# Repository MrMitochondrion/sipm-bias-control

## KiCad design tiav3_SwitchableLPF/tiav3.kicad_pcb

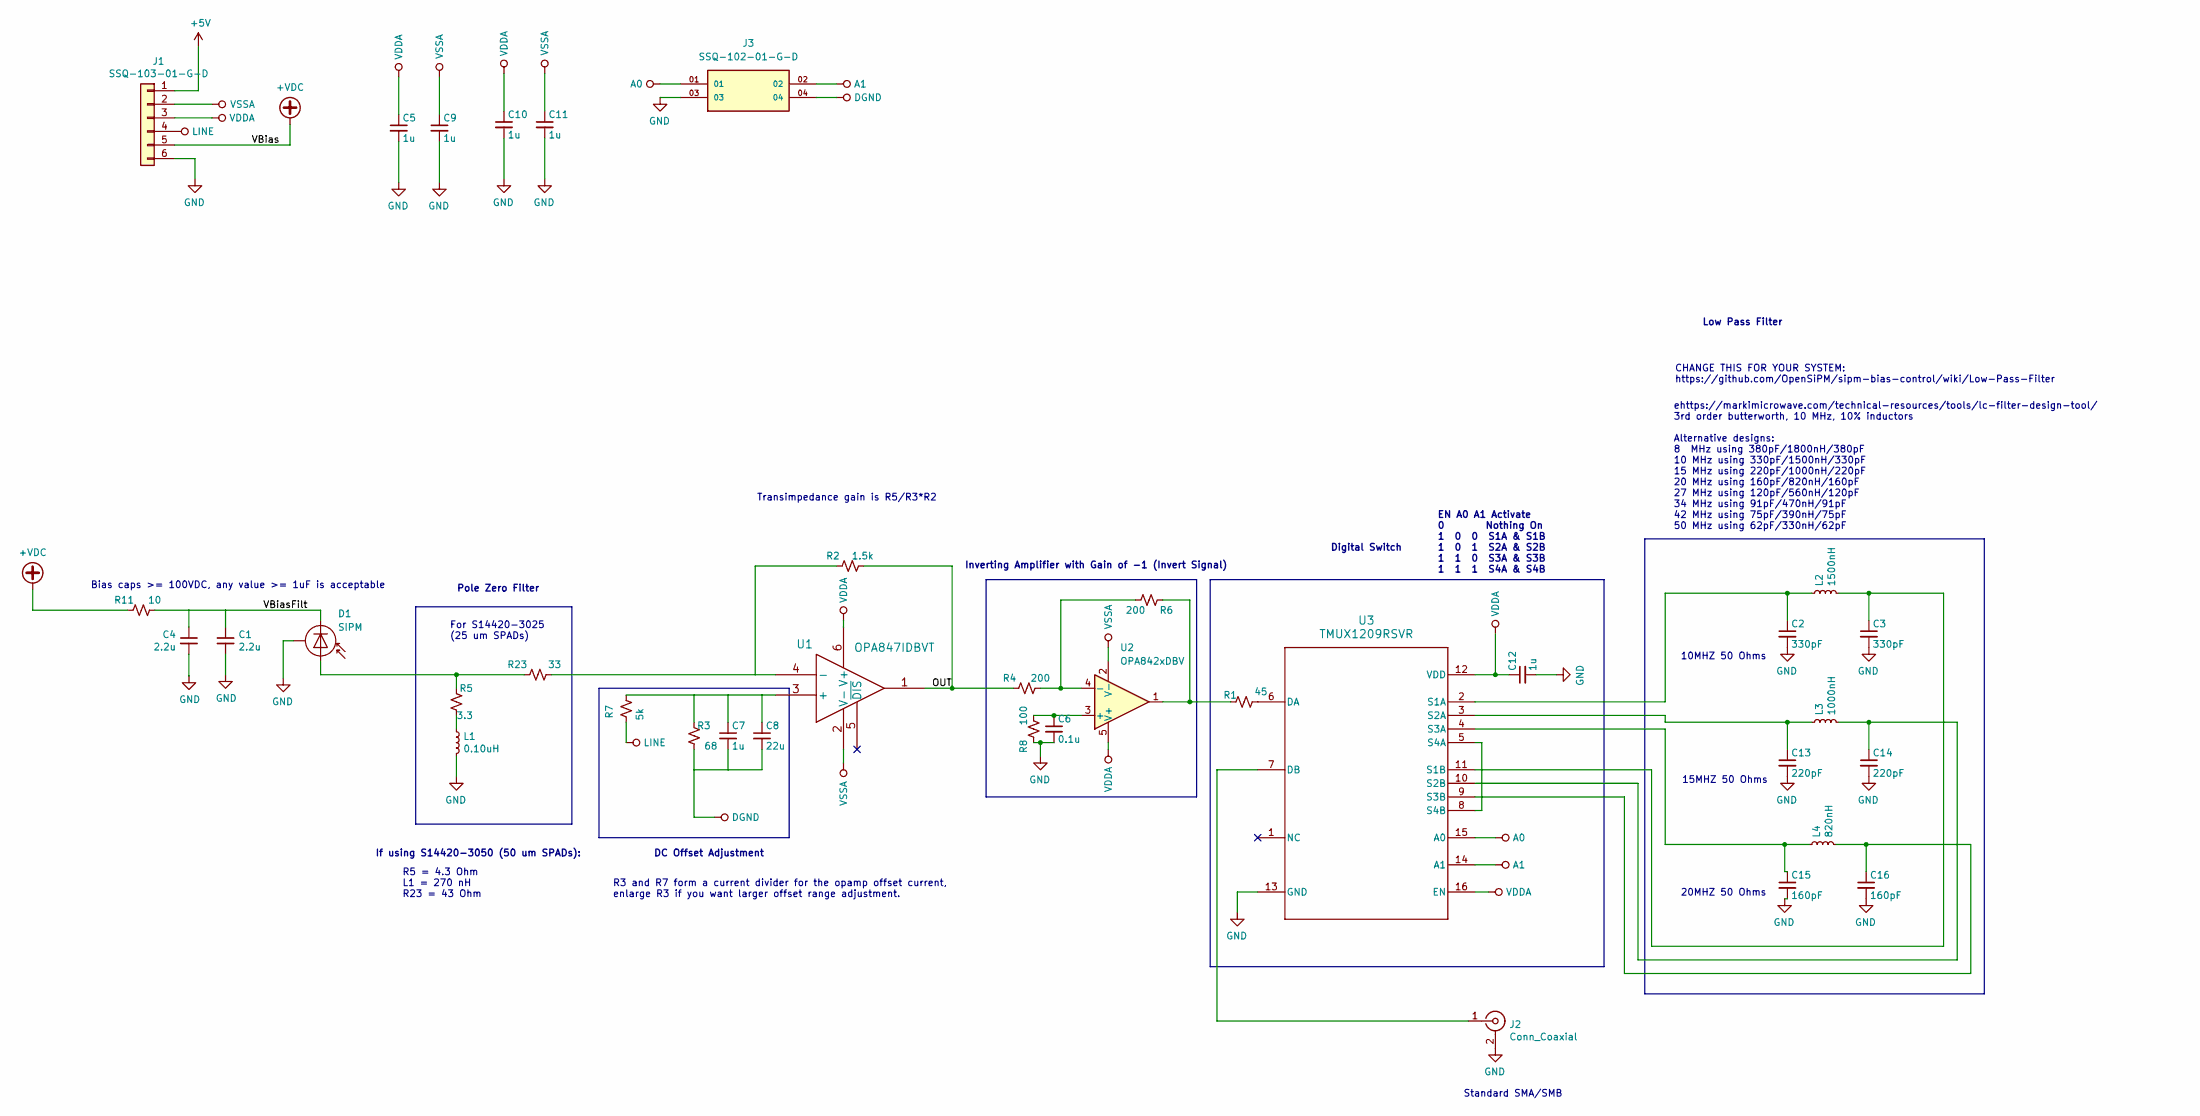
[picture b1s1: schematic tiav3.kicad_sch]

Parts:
C1, C4: 2.2u; C_1206_3216Metric_Pad1.33x1.80mm_HandSolder; Voltage 100V
C2, C3: 330pF; C_0402_1005Metric_Pad0.74x0.62mm_HandSolder
C5, C9, C10, C11: 1u; C_0402_1005Metric; Voltage 10V
C6: 0.1u; C_0402_1005Metric
C7, C12: 1u; C_0402_1005Metric
C8: 22u; C_0603_1608Metric
C13, C14: 220pF; C_0402_1005Metric_Pad0.74x0.62mm_HandSolder
C15, C16: 160pF; C_0402_1005Metric_Pad0.74x0.62mm_HandSolder
D1: SIPM; S14420
J1: SSQ-103-01-G-D; PinHeader_2x03_P2.54mm_Vertical
J2: Conn_Coaxial; SMB_Jack_Vertical; Digikey WM5528-ND
J3: SSQ-102-01-G-D; SAMTEC_SSQ-102-01-G-D; PARTREV R
L1: 0.10uH; L_0603_1608Metric_Pad1.05x0.95mm_HandSolder
L2: 1500nH; L_0603_1608Metric; part MLF1005GR56JTD25
L3: 1000nH; L_0603_1608Metric; part MLF1005GR56JTD25
L4: 820nH; L_0603_1608Metric; part MLF1005GR56JTD25
R1: 45; R_0402_1005Metric_Pad0.72x0.64mm_HandSolder
R2: 1.5k; R_0402_1005Metric_Pad0.72x0.64mm_HandSolder
R3: 68; R_0402_1005Metric_Pad0.72x0.64mm_HandSolder
R4, R6: 200; R_0402_1005Metric_Pad0.72x0.64mm_HandSolder
R5: 3.3; R_0402_1005Metric_Pad0.72x0.64mm_HandSolder
R7: 5k; R_0402_1005Metric_Pad0.72x0.64mm_HandSolder
R8: 100; R_0402_1005Metric_Pad0.72x0.64mm_HandSolder
R11: 10; R_0402_1005Metric_Pad0.72x0.64mm_HandSolder
R23: 33; R_0402_1005Metric_Pad0.72x0.64mm_HandSolder
U1: OPA847IDBVT
U2: OPA842xDBV; SOT-23-5
U3: TMUX1209RSVR; RSV0016A

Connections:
+5V: J1.1
+VDC: J1.5, R11.1
/OUT: R2.2, R4.1, U1.1
/VBiasFilt: C1.1, C4.1, D1.1 (K), R11.2
A0: J3.01, U3.15 (A0)
A1: J3.02, U3.14 (A1)
DGND: C7.2, C8.2, J3.04, R3.1
GND: C1.2, C2.2, C3.2, C4.2, C5.2, C6.2, C9.2, C10.2, C11.2, C12.2, C13.2, C14.2, C15.2, C16.2, D1.3 (CASE), J1.6, J2.2 (Ext), J3.03, L1.2, R8.1, U3.13 (GND)
LINE: J1.4, R7.2
unnamed: D1.2 (A), R5.2, R23.1
unnamed: J2.1 (In), U3.7 (DB)
unnamed: L1.1, R5.1
unnamed: R1.1, R6.1, U2.1
unnamed: C7.1, C8.1, R3.2, R7.1, U1.3 (+)
unnamed: R2.1, R23.2, U1.4 (-)
unnamed: C6.1, R8.2, U2.3 (+)
unnamed: R4.2, R6.2, U2.4 (-)
unnamed: R1.2, U3.6 (DA)
unnamed: C2.1, L2.1, U3.2 (S1A)
unnamed: C3.1, L2.2, U3.11 (S1B)
unnamed: C13.1, L3.1, U3.3 (S2A)
unnamed: C14.1, L3.2, U3.10 (S2B)
unnamed: C15.1, L4.1, U3.4 (S3A)
unnamed: C16.1, L4.2, U3.9 (S3B)
unnamed: U3.5 (S4A), U3.8 (S4B)
VDDA: C5.1, C10.1, C12.1, J1.3, U1.6 (V+), U2.5 (V+), U3.12 (VDD), U3.16 (EN)
VSSA: C9.1, C11.1, J1.2, U1.2 (V-), U2.2 (V-)

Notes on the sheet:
If using S14420-3050 (50 um SPADs):
R5 = 4.3 Ohm L1 = 270 nH R23 = 43 Ohm
Bias caps >= 100VDC, any value >= 1uF is acceptable
EN A0 A1 Activate 0 Nothing On 1 0 0 S1A & S1B 1 0 1 S2A & S2B 1 1 0 S3A & S3B 1 1 1 S4A & S4B
R3 and R7 form a current divider for the opamp offset current, enlarge R3 if you want larger offset range adjustment.
Pole Zero Filter
Inverting Amplifier with Gain of -1 (Invert Signal)
For S14420-3025 (25 um SPADs)
Standard SMA/SMB
Digital Switch
10MHZ 50 Ohms
15MHZ 50 Ohms
Low Pass Filter
CHANGE THIS FOR YOUR SYSTEM: https://github.com/OpenSiPM/sipm-bias-control/wiki/Low-Pass-Filter
Transimpedance gain is R5/R3*R2
20MHZ 50 Ohms
DC Offset Adjustment
ehttps://markimicrowave.com/technical-resources/tools/lc-filter-design-tool/ 3rd order butterworth, 10 MHz, 10% inductors Alternative designs: 8 MHz using 380pF/1800nH/380pF 10 MHz using 330pF/1500nH/330pF 15 MHz using 220pF/1000nH/220pF 20 MHz using 160pF/820nH/160pF 27 MHz using 120pF/560nH/120pF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

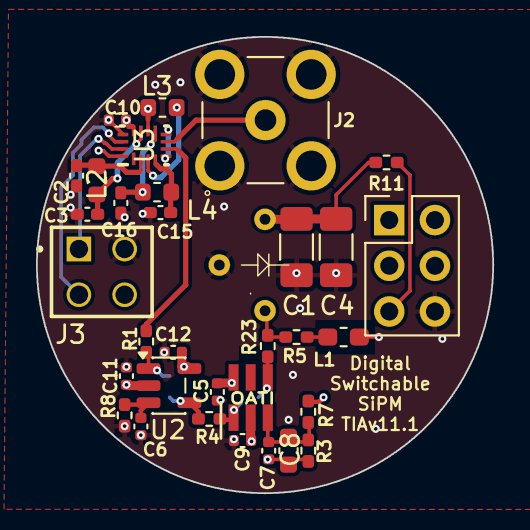
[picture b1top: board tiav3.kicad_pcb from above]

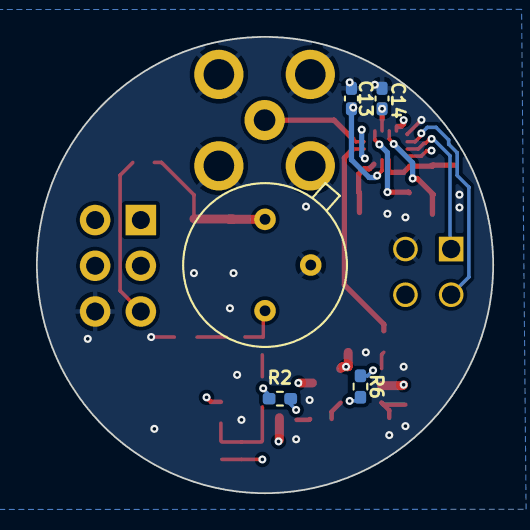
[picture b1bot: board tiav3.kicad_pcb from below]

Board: 4 copper layers, 25.3 x 25.3 mm, 37 parts (5 on the bottom side), 26 nets.

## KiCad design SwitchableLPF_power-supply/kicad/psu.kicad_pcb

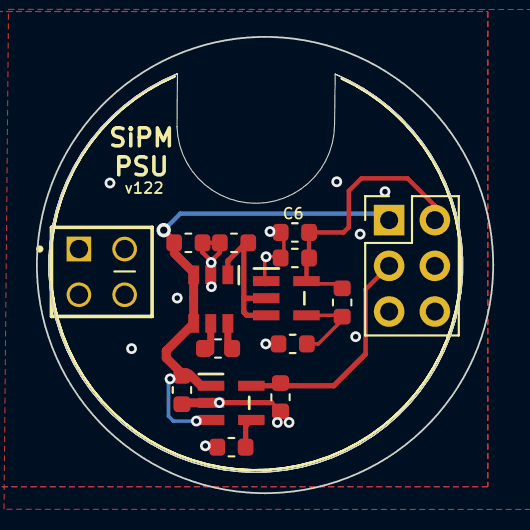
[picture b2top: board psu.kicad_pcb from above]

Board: 2 copper layers, 25.3 x 25.3 mm, 15 parts (0 on the bottom side), 9 nets.

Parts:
C1, C3, C5, C6, C15: 22u; C_0603_1608Metric
C2: 1u; C_0603_1608Metric
C8: 1uF; C_0603_1608Metric
C17: 10n; C_0603_1608Metric
J3: SSQ-103-03-G-D; PinHeader_2x03_P2.54mm_Vertical
J3#2: SSQ-102-01-G-D; SAMTEC_SSQ-102-01-G-D
R8: 64.9k; R_0603_1608Metric
R9: 24.9k; R_0603_1608Metric
U1: LM2776; LM2776DBVR
U3: TPS72301DBVR
U5: TPS79333DBVR

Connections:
+5V: C1.2, C2.2, J3.1, U1.3 (Vin), U1.4 (EN), U5.1 (IN), U5.3 (EN)
-5V: C15.2, U1.1 (Vout), U3.2 (IN), U3.3 (EN)
GND: C1.1, C2.1, C3.1, C5.1, C6.1, C15.1, C17.1, J3.6, J3#2.03, R9.1, U1.2 (GND), U3.1 (GND), U5.2 (GND)
unnamed: C8.1, U1.6 (C1-)
unnamed: C8.2, U1.5 (C1+)
unnamed: C17.2, U5.4 (NR)
unnamed: R8.1, R9.2, U3.4 (FB)
VDDA: C3.2, J3.3, U5.5 (OUT)
VSSA: C5.2, C6.2, J3.2, R8.2, U3.5 (OUT)

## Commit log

2026-06-25 Fix print statement
    We don't use the MCP4728 in the newer bias gen.
2026-06-29 Created digitally switchable LPF SiPM based on tiav_14420
2026-06-29 Performed claude analysis on the project and fixed risk 4
2026-06-30 Created the 50 ohm impedance and changed EN pin to Ground
2026-06-30 Changed the Power Supply to Fit the New SiPM

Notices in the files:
parts and their libraries:
Copyright 2016 Accelerated Designs. All rights reserved.
